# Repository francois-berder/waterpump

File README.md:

# Waterpump

This project is an automatic system for watering plants. Everyday, pumps are switched on for a few seconds to provide enough water to some plants. The device can be controlled by sending SMS to change the schedule or water plants. In addition, a small push-button is present to water plants immediately.

## Build and flash instructions

### Prerequisites

You need to install the [ARM embedded toolchain](https://developer.arm.com/tools-and-software/open-source-software/developer-tools/gnu-toolchain/gnu-rm) and [JLink Software and Documentation Pack](https://www.segger.com/downloads/jlink/#J-LinkSoftwareAndDocumentationPack).

### SIM card configuration

The SIM card might need to be unlocked. The default PIN is set to 1234 by the `SIMCARD_PIN` macro that can be overriden.

To retrieve time from network, the firmware needs the APN name which depends on your
network provider. The macro `SIM800_APN_NAME` is currently set to `"free"` in the Makefile because I am using a SIM card from Free Mobile. Feel free to change it.

### Commands

There are two types of build: release and debug.

To build the project, run one of these commands:
```
$ make                  # BUILDTYPE set to release
$ BUILDTYPE=release make
$ BUILDTYPE=debug make
```

Connect the board to a SEGGER debug probe and run these commands to flash or debug the firmware:
```
$ make flash-target                 # Flash release firmware
$ BUILDTYPE=debug make flash-target # Flash debug firmware
$ BUILDTYPE=debug make debug-target # Start debugging firmware
```

## Building hardware

In `hardware` folder, there are Gerber files sent to [JLCPCB](https://jlcpcb.com/) for each revision of the board. I recommend that you build the latest revision of the board. Components can be bought on [RS online](https://uk.rs-online.com/web/).

### Issues with rev1 board

  * SIM800L Footprint is incorrect
  * No mounting holes
  * micro USB connector is too far away from the side of the board
  * Power circuit for SIM800L is not working properly. Large polarized capacitors are missing on the input and output of the LDO voltage regulator. The regulator is not able to handle load transients fast enough, causing the SIM800L to brown out.

### Issues with rev2 board

  * SIM800L footprint is still incorrect ! Although it is easier to insert the module in pin headers than on rev1.
  * micro USB connector should be replaced by a barrel connector because USB cables should not be used to provide 3A.

## Power requirements

The GSM module can use up to 2A and each pump should not use more than 1A due to the choice of MOSFET transistors (especially on rev 2).
For this reason, I recommend powering this board with a 5V 3A power supply. Alternatively if you are using only 2.5W pumps, a 5V 2.5A can be used.

## Switching on water pump

Both pumps are switched on in sequence for 3 seconds each if the push button is pressed or if the GSM modules receives a text message starting with "WATER ALL". If you only want to enable pump 1 or 2, send text message "WATER 1" or "WATER 2".

## SMS commands

| Command | description | examples |
| --- | ----------- | ------- |
| `BUTTON <duration>` | Configure for how long each pump is enabled when button is pressed | `BUTTON 5` |
| `WATER <pump_index>` | Turn on one pump for `DEFAULT_PUMP_DURATION` seconds (default: 3s) | `WATER 1`, `WATER 2` |
| `WATER ALL` | Turn on both pumps, each for `DEFAULT_PUMP_DURATION` seconds (default: 3s)| `WATER ALL` |
| `SCHEDULE <index> STOP` | Disable a schedule| `SCHEDULE 0 STOP`, `SCHEDULE 1 STOP` |
| `SCHEDULE <index> <hour>:<min>:<sec> <duration> ALL` | Turn on both pumps once per day | `SCHEDULE 0 19:04:57 3 ALL` |
| `SCHEDULE <index> <hour>:<min>:<sec> <duration> <pump_index>` | Turn on a pump once per day | `SCHEDULE 2 06:43:00 7 1`, `SCHEDULE 3 06:43:00 9 2` |
| `SCHEDULE STATUS` | Request schedule status | `SCHEDULE STATUS` |

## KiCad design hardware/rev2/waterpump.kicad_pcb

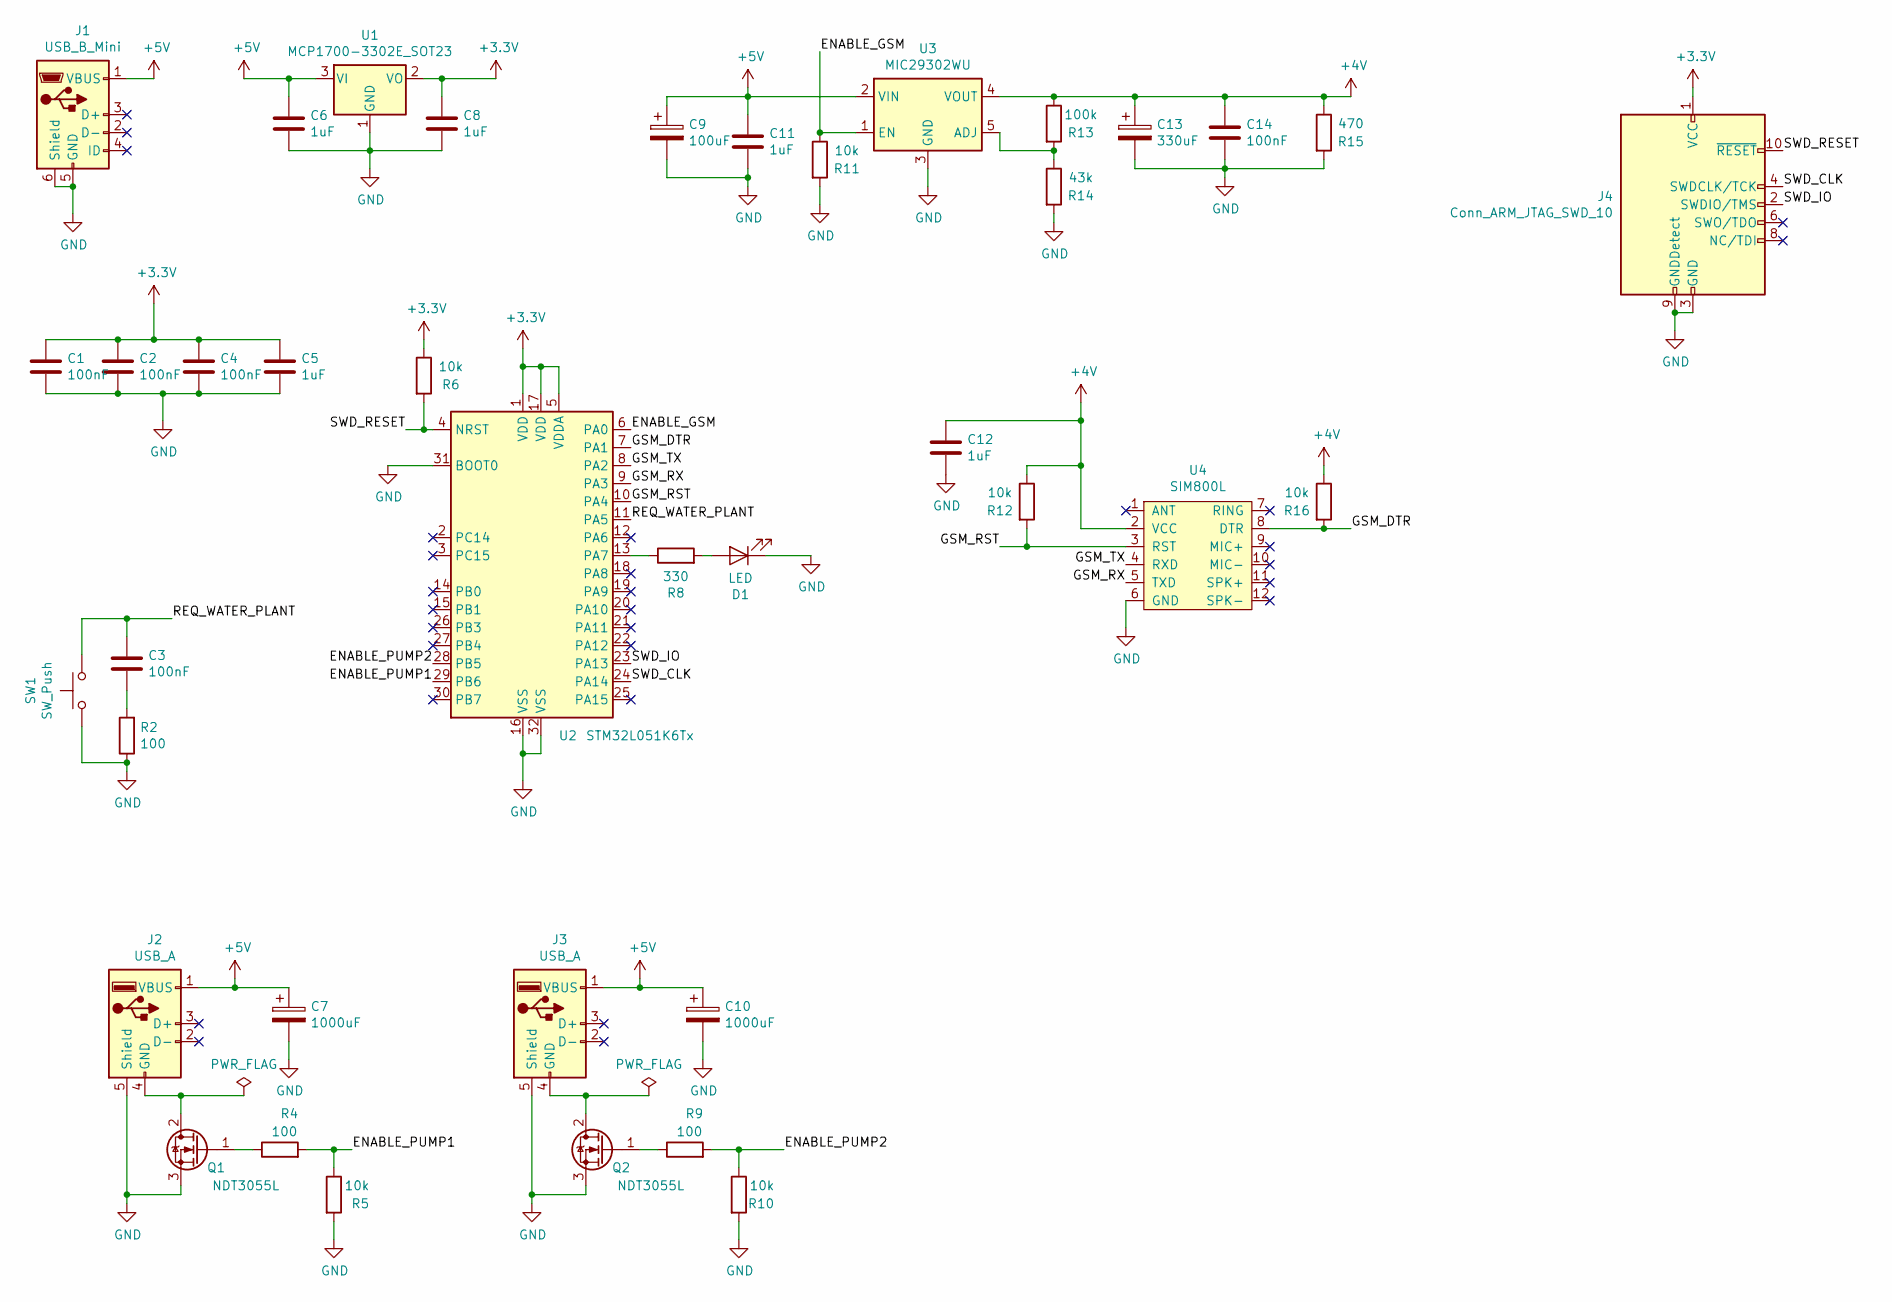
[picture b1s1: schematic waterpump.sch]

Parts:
C1, C2, C3, C4, C14: 100nF; C_0805_2012Metric
C5, C6, C8, C11, C12: 1uF; C_0805_2012Metric
C7, C10: 1000uF; CP_Radial_D10.0mm_P5.00mm
C9: 100uF; CP_Radial_D6.3mm_P2.50mm
C13: 330uF; CP_Radial_D8.0mm_P3.50mm
D1: LED; LED_0805_2012Metric
J1: USB_B_Mini; USB_Mini-B_Lumberg_2486_01_Horizontal
J2, J3: USB_A; USB_A_Stewart_SS-52100-001_Horizontal
J4: Conn_ARM_JTAG_SWD_10; PinHeader_2x05_P1.27mm_Vertical_SMD
Q1, Q2: NDT3055L; SOT-223-3_TabPin2
R2, R4, R9: 100; R_0805_2012Metric
R5, R6, R10, R11, R12, R16: 10k; R_0805_2012Metric
R8: 330; R_0805_2012Metric
R13: 100k; R_0805_2012Metric
R14: 43k; R_0805_2012Metric
R15: 470; R_0805_2012Metric
SW1: SW_Push; SW_Tactile_SKHH_Angled
U1: MCP1700-3302E_SOT23; SOT-23
U2: STM32L051K6Tx; LQFP-32_7x7mm_P0.8mm
U3: MIC29302WU; TO-263-5_TabPin3
U4: SIM800L

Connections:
+3V3: C1.1, C2.1, C4.1, C5.1, C8.1, J4.1 (VCC), R6.1, U1.2 (VO), U2.1 (VDD), U2.5 (VDDA), U2.17 (VDD)
+4V: C12.1, C13.1, C14.1, R12.1, R13.1, R15.1, R16.1, U3.4 (VOUT), U4.2 (VCC)
+5V: C6.1, C7.1, C9.1, C10.1, C11.1, J1.1 (VBUS), J2.1 (VBUS), J3.1 (VBUS), U1.3 (VI), U3.2 (VIN)
/ENABLE_GSM: R11.1, U2.6 (PA0), U3.1 (EN)
/ENABLE_PUMP1: R4.2, R5.1, U2.29 (PB6)
/ENABLE_PUMP2: R9.2, R10.1, U2.28 (PB5)
/GSM_DTR: R16.2, U2.7 (PA1), U4.8 (DTR)
/GSM_RST: R12.2, U2.10 (PA4), U4.3 (RST)
/GSM_RX: U2.9 (PA3), U4.5 (TXD)
/GSM_TX: U2.8 (PA2), U4.4 (RXD)
/REQ_WATER_PLANT: C3.1, SW1.2, U2.11 (PA5)
/SWD_CLK: J4.4 (SWDCLK/TCK), U2.24 (PA14)
/SWD_IO: J4.2 (SWDIO/TMS), U2.23 (PA13)
/SWD_RESET: J4.10 (~RESET~), R6.2, U2.4 (NRST)
GND: C1.2, C2.2, C4.2, C5.2, C6.2, C7.2, C8.2, C9.2, C10.2, C11.2, C12.2, C13.2, C14.2, D1.1 (K), J1.5 (GND), J1.6 (Shield), J2.5 (Shield), J3.5 (Shield), J4.3 (GND), J4.5 (GND), J4.9 (GNDDetect), Q1.3 (S), Q2.3 (S), R2.1, R5.2, R10.2, R11.2, R14.2, R15.2, SW1.1, U1.1 (GND), U2.16 (VSS), U2.31 (BOOT0), U2.32 (VSS), U3.3 (GND), U4.6 (GND)
unnamed: C3.2, R2.2
unnamed: D1.2 (A), R8.2
unnamed: J2.4 (GND), Q1.2 (D)
unnamed: J3.4 (GND), Q2.2 (D)
unnamed: Q1.1 (G), R4.1
unnamed: Q2.1 (G), R9.1
unnamed: R8.1, U2.13 (PA7)
unnamed: R13.2, R14.1, U3.5 (ADJ)

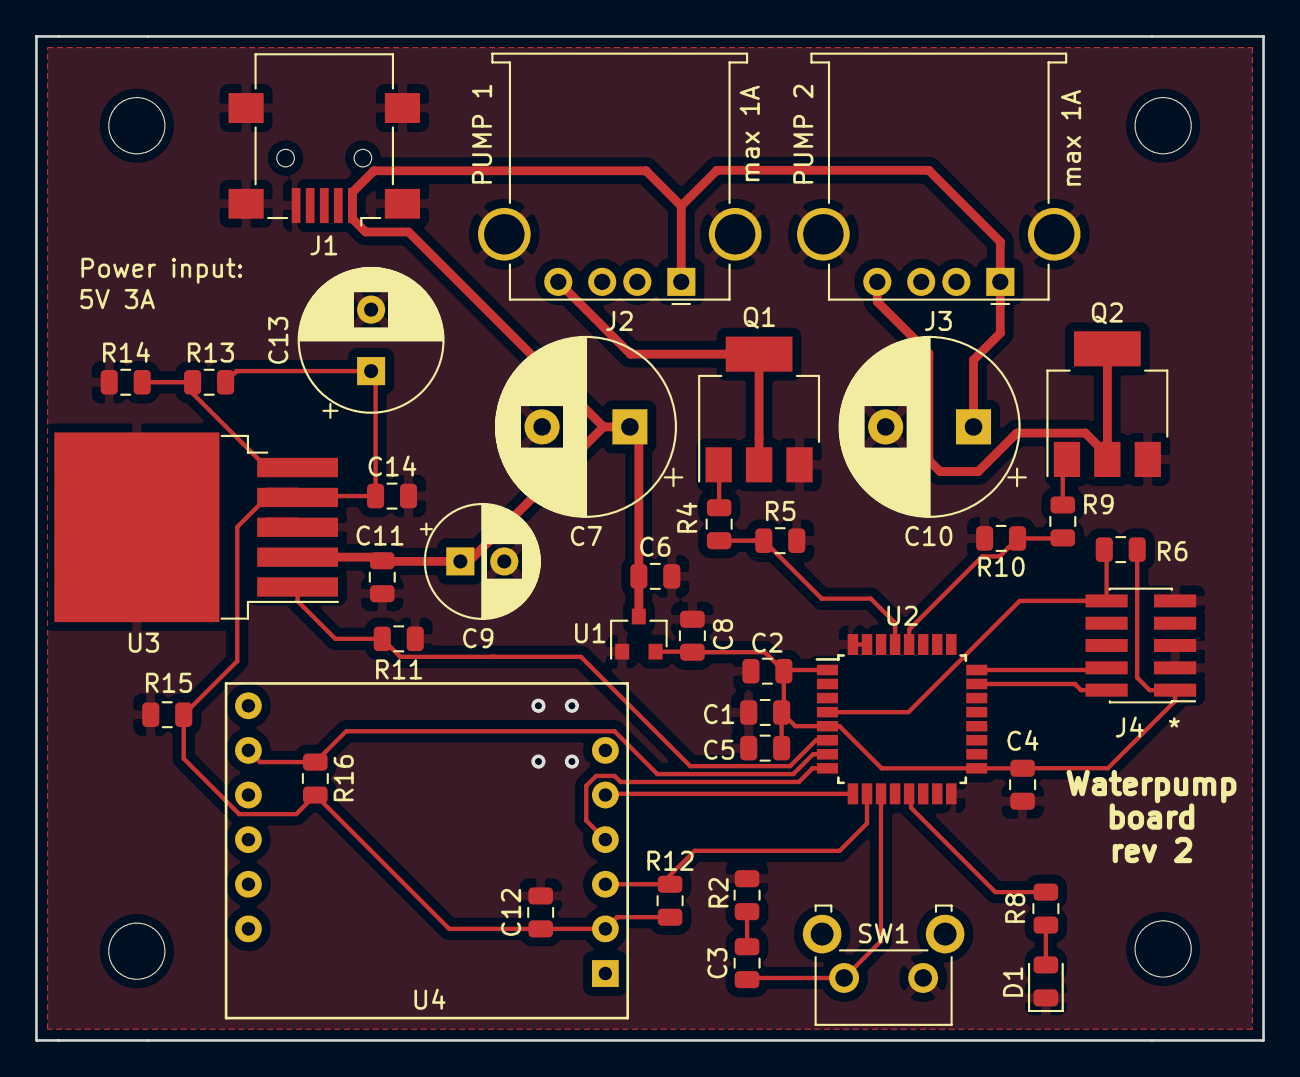
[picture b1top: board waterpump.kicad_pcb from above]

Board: 2 copper layers, 69.8 x 57.2 mm, 39 parts (0 on the bottom side), 23 nets.

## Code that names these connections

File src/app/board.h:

/*
 * Copyright (C) 2019 Francois Berder <fberder@outlook.fr>
 *
 * This file is part of waterpump.
 *
 * waterpump is free software: you can redistribute it and/or modify
 * it under the terms of the GNU General Public License as published by
 * the Free Software Foundation, either version 3 of the License, or
 * (at your option) any later version.
 *
 * waterpump is distributed in the hope that it will be useful,
 * but WITHOUT ANY WARRANTY; without even the implied warranty of
 * MERCHANTABILITY or FITNESS FOR A PARTICULAR PURPOSE.  See the
 * GNU General Public License for more details.
 *
 * You should have received a copy of the GNU General Public License
 * along with waterpump.  If not, see <http://www.gnu.org/licenses/>.
 */

#ifndef BOARD_H
#define BOARD_H

#include "app/sim800l.h"
#include "mcu/gpio.h"

#define ENABLE_GSM_PIN      (GPIO_PIN(PORT_A, 0))
#define ENABLE_PUMP1_PIN    (GPIO_PIN(PORT_B, 6))
#define ENABLE_PUMP2_PIN    (GPIO_PIN(PORT_B, 5))
#define LED_PIN             (GPIO_PIN(PORT_A, 7))
#define REQ_WATER_PIN       (GPIO_PIN(PORT_A, 5))
#define GSM_TX_PIN          (GPIO_PIN(PORT_A, 2))
#define GSM_RX_PIN          (GPIO_PIN(PORT_A, 3))

#define CORE_CLOCK          (4190000)
#define CLOCK_APB1          (CORE_CLOCK)
#define CLOCK_APB2          (CORE_CLOCK)

#define MCU_TIM2_EN     /* Used by pumps module */
#define MCU_TIM21_EN    /* Used by SIM800 module */
#define MCU_TIM22_EN    /* Used by status module */
#define MCU_UART_EN

#define SIM800_USART        (USART2)

#endif

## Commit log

2019-09-09 Initial import
2019-09-12 Implement RTC wake up timer driver
2019-09-12 Do not enable NVIC interrupt in GPIO driver
2019-09-12 Move pins definitions to board.h
    Also define clock speeds
2019-09-12 Configure clocks at boot
2019-09-15 makefile: Rename CONFIG to BUILDTYPE
2019-09-15 Add readme
2019-09-26 makefile: Add -nostartfiles linker option
2019-09-26 tools: Use SWD to communicate with the ARM core
2019-09-26 makefile: Define JLINK_DEVICE
2019-09-26 Fix GPIO HAL
2019-09-26 Configure interrupt and callback for req water button
2019-09-26 Implement timer HAL
2019-09-26 Enable pumps for 3 second when button is pressed
2019-09-26 Sleep in main loop
2019-09-28 docs: Rename stm32l051k6 datasheet
2019-09-28 docs: Add stm32l051xx reference manual
2019-09-28 Configure GSM TX/RX pins
2019-09-28 docs: Add SIM800 AT commands manual v1.09
2019-09-28 Implement UART HAL
2019-09-29 Implement mcu_delay
2019-10-02 Implement uart_receive_noblock
2019-10-03 Sleep in mcu_delay
2019-10-03 Replace uart_receive_noblock by UART RX INT
2019-10-03 Initialize SIM800L module
2019-10-03 Check SIM card presence
2019-10-04 Refactor gsm initialization
2019-10-04 Add missing volatile qualifier
2019-10-05 fixup! Refactor gsm initialization
2019-10-05 Set SMS format to text during gsm initialization
2019-10-05 Use SIM card to store SMS
2019-10-06 Fix timer 21/22 interrupt handler
2019-10-06 Refactor handling of SIM800 replies
2019-10-06 Implement sim800l_delete_sms
2019-10-06 Use AT+CMGDA to delete all SMS
2019-10-06 Implement sim800l_delete_all_received_sms
2019-10-08 Enable pumps when receiving SMS
    SMS text must start with "REQ WATER" to enable the pumps.
2019-10-08 Implement sim800l_get_time
2019-10-08 Implement sim800l_send_sms
2019-10-08 Make sure that all characters are sent before leaving uart_send
2019-10-08 Check if SIM card was unlocked
2019-10-12 Return correct status if SIM800L is looking for network
2019-10-12 Implement sim800l_connect_to_network
2019-10-12 Fix documentation for sim800l_check_network_registration
2019-10-12 Continuously try to connect to 2G network
2019-10-15 Fix initialization of GSM module
2019-10-17 hardware: Add rev1 Kicad files
2019-10-17 hardware: Add rev1 factory files
2019-10-17 docs: Add SIM800 Hardware design guide
2019-10-17 fixup! hardware: Add rev1 factory files
2019-10-20 hardware: Add Kicad files for rev2 board
2019-10-20 hardware: Add files for rev2 board sent to factory
2019-10-20 Enable pumps in sequence
    Both pumps and GSM cannot be all on at the same time
    as they might use too much power.
2019-10-20 readme: Add info about power requirements and how to switch on the pump
2019-10-22 readme: Add info on how to build hardware and add list of defects of rev1
2019-10-28 Ensure pump 2 is off for a second before stopping pumps module
2019-10-28 Enhance pumps module to enable only one pump
2019-11-09 Allow starting only one pump via SMS
2019-11-09 docs: Add schematics for rev2
2019-11-09 readme: Update text message to enable pumps
2019-11-09 Change ENABLE_GSM pin for rev2 board
2019-11-09 Fix length check in handle_sms
2019-11-09 Use internal pull-up on REQ_WATER pin
2019-11-09 readme: Add rev2 board issues
2019-11-16 Disable GSM after 10 consecutive errors
2019-11-16 readme: Mention plants watering can be triggered by a text message
2019-11-16 Revert "Implement RTC wake up timer driver"
    This reverts commit e43a198a27f5da32a88bd026057ed1c3d6771577.
2019-11-16 readme: Add rev 2 board image
2019-11-16 mcu: Fix TIM22 driver
2019-11-16 app: Blink LED while pumps are enabled
2019-11-17 Implement sim800l_enable_time
2019-11-17 Implement rtc initialization
2019-11-17 mcu: Implement eeprom driver
2019-11-17 ldscripts: Add section to store data in eeprom
2019-12-15 mcu: Implement RTC alarm
2019-12-17 Implement schedule
2019-12-17 Configure schedule by SMS
2019-12-17 readme: Add issue about power connector on rev2 board
2020-01-04 apps: firmware: Contact 2G network to retrieve time
2020-01-04 readme: Add SMS commands list
2020-01-04 readme: Add doc on SIM card configuration
2020-01-04 readme: Remove warning about ongoing project
2020-01-04 app: Ensure schedule is valid before using it
2020-01-05 Improve reliability when parsing sms
2020-01-05 Send schedule status by SMS
2020-01-05 Improve parsing SMS reliability
2020-01-05 Fix parsing SIM800 RTC time
2020-01-05 Remove one level of indentation in main
2020-01-05 readme: Fix sms commands
2020-01-07 app: Allow turning on pumps for a variable amount of time
2020-01-07 app: Allow override of SIMCARD_PIN macro
2020-01-07 app: Allow override of DEFAULT_PUMP_DURATION macro
2020-01-07 readme: Mention how to change default SIM card PIN
2020-01-07 app: Do not show time, pump if schedule is off
2020-01-07 app: Print duration in schedule_to_string
2020-01-16 app: Ensure RTC is initialized properly upon boot
2020-01-16 mcu: Implement rtc_get_time
2020-01-16 mcu: Implement rtc_set_prescaler
2020-01-16 mcu: Set RTC prescalers to default value in rtc_init
2020-01-16 app: Calibrate LSI clock
2020-01-16 readme: Mention issue with LSI clock
2020-01-16 app: Remove todo
2020-01-26 app: Implement delete/set alarm in SIM800
2020-01-26 Rely entirely on SIM800 RTC
2020-01-26 Remove MAX_SIM800_ALARM macro
2020-01-29 Reduce Vcore to 1.2V
2020-01-29 Reduce core clock to 4.2MHz
2020-01-29 Fix scheduling
2020-01-29 readme: Update SCHEDULE SMS commands
2020-01-29 Turn off LED by default
2020-01-30 Configure pump duration if buttton pressed
2020-01-30 readme: Document BUTTON command
2020-01-30 readme: Improve documentation for WATER commands
2020-01-30 readme: Small update
2020-02-02 Remove leading whitespaces before parsing sms content
2020-02-02 Fix parsing SCHEDULE command
2020-02-02 Fix bug in schedule_configure
2021-11-17 Add .circleci/config.yml
